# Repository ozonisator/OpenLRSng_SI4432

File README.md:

OpenLRSng Empfänger mit SI4432 Breakoutboard. Kompatibel zu "DTFUHF 4ch RX"

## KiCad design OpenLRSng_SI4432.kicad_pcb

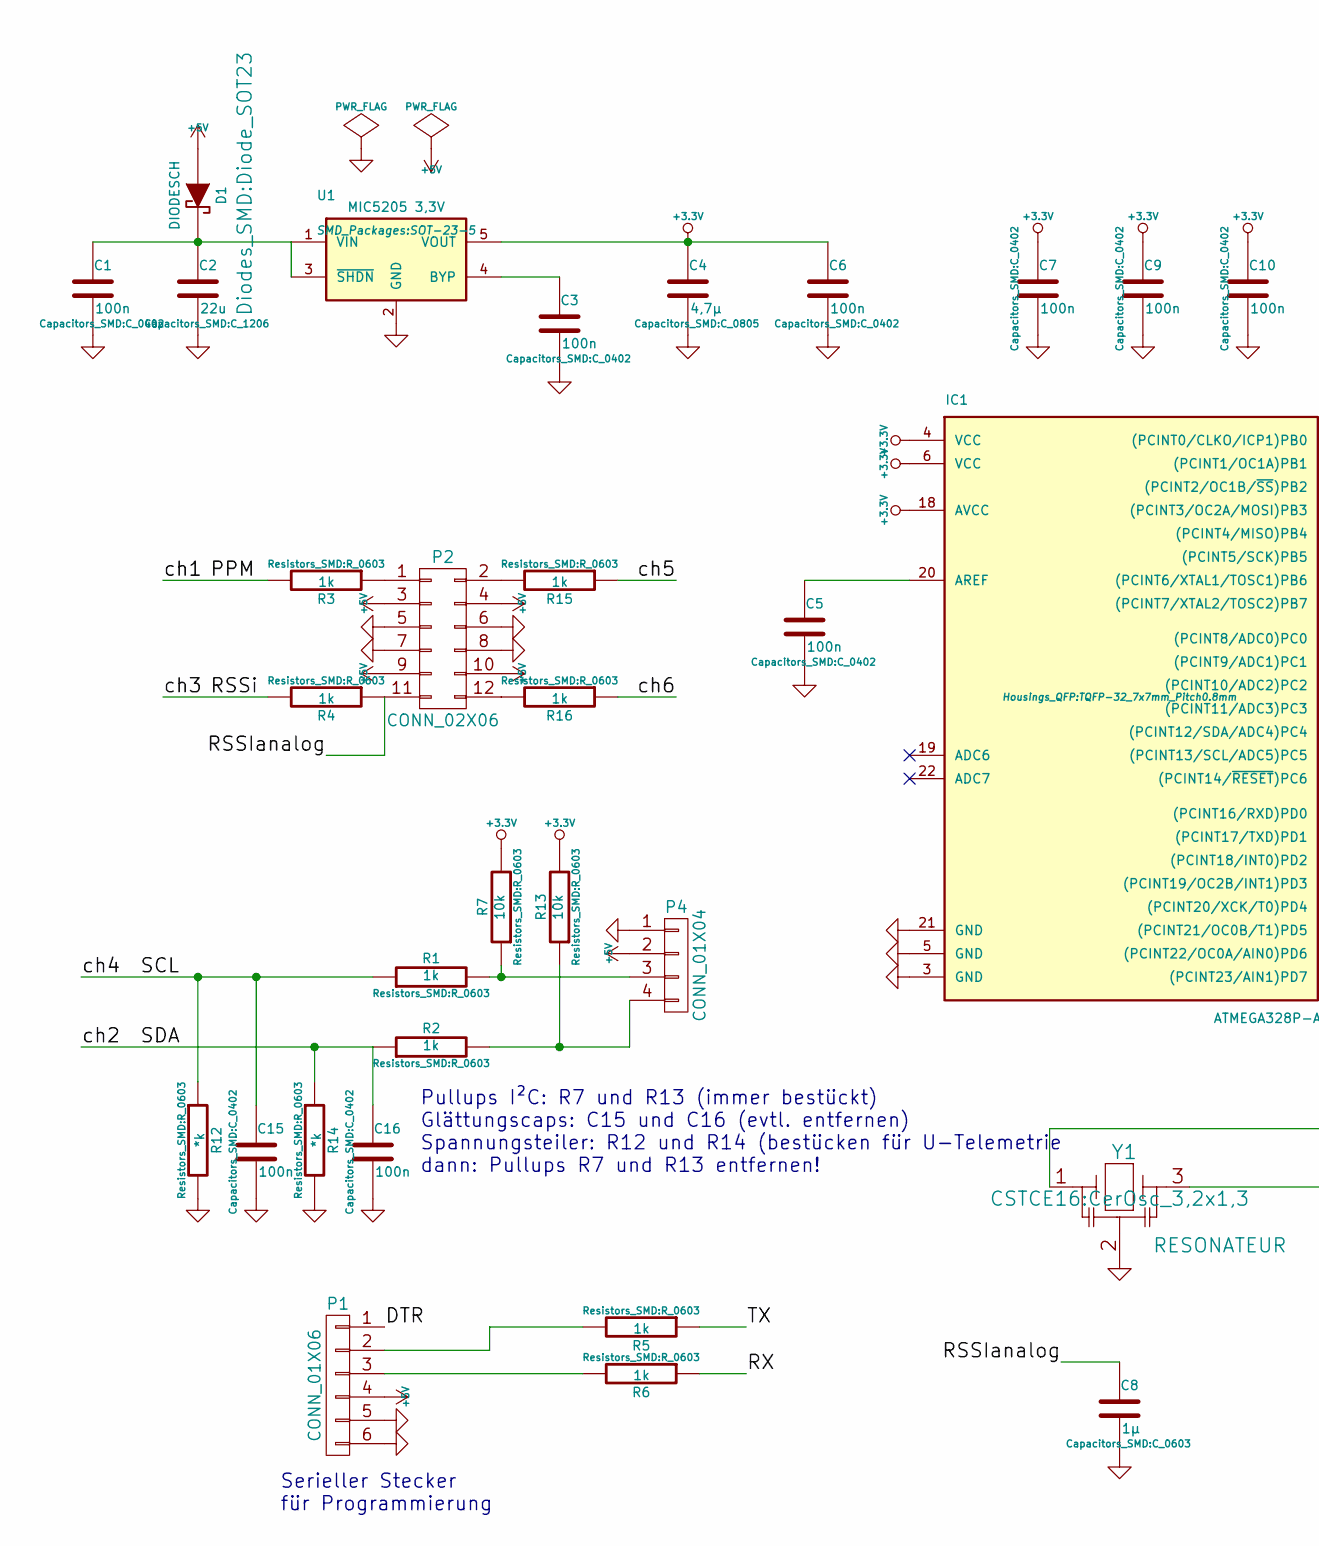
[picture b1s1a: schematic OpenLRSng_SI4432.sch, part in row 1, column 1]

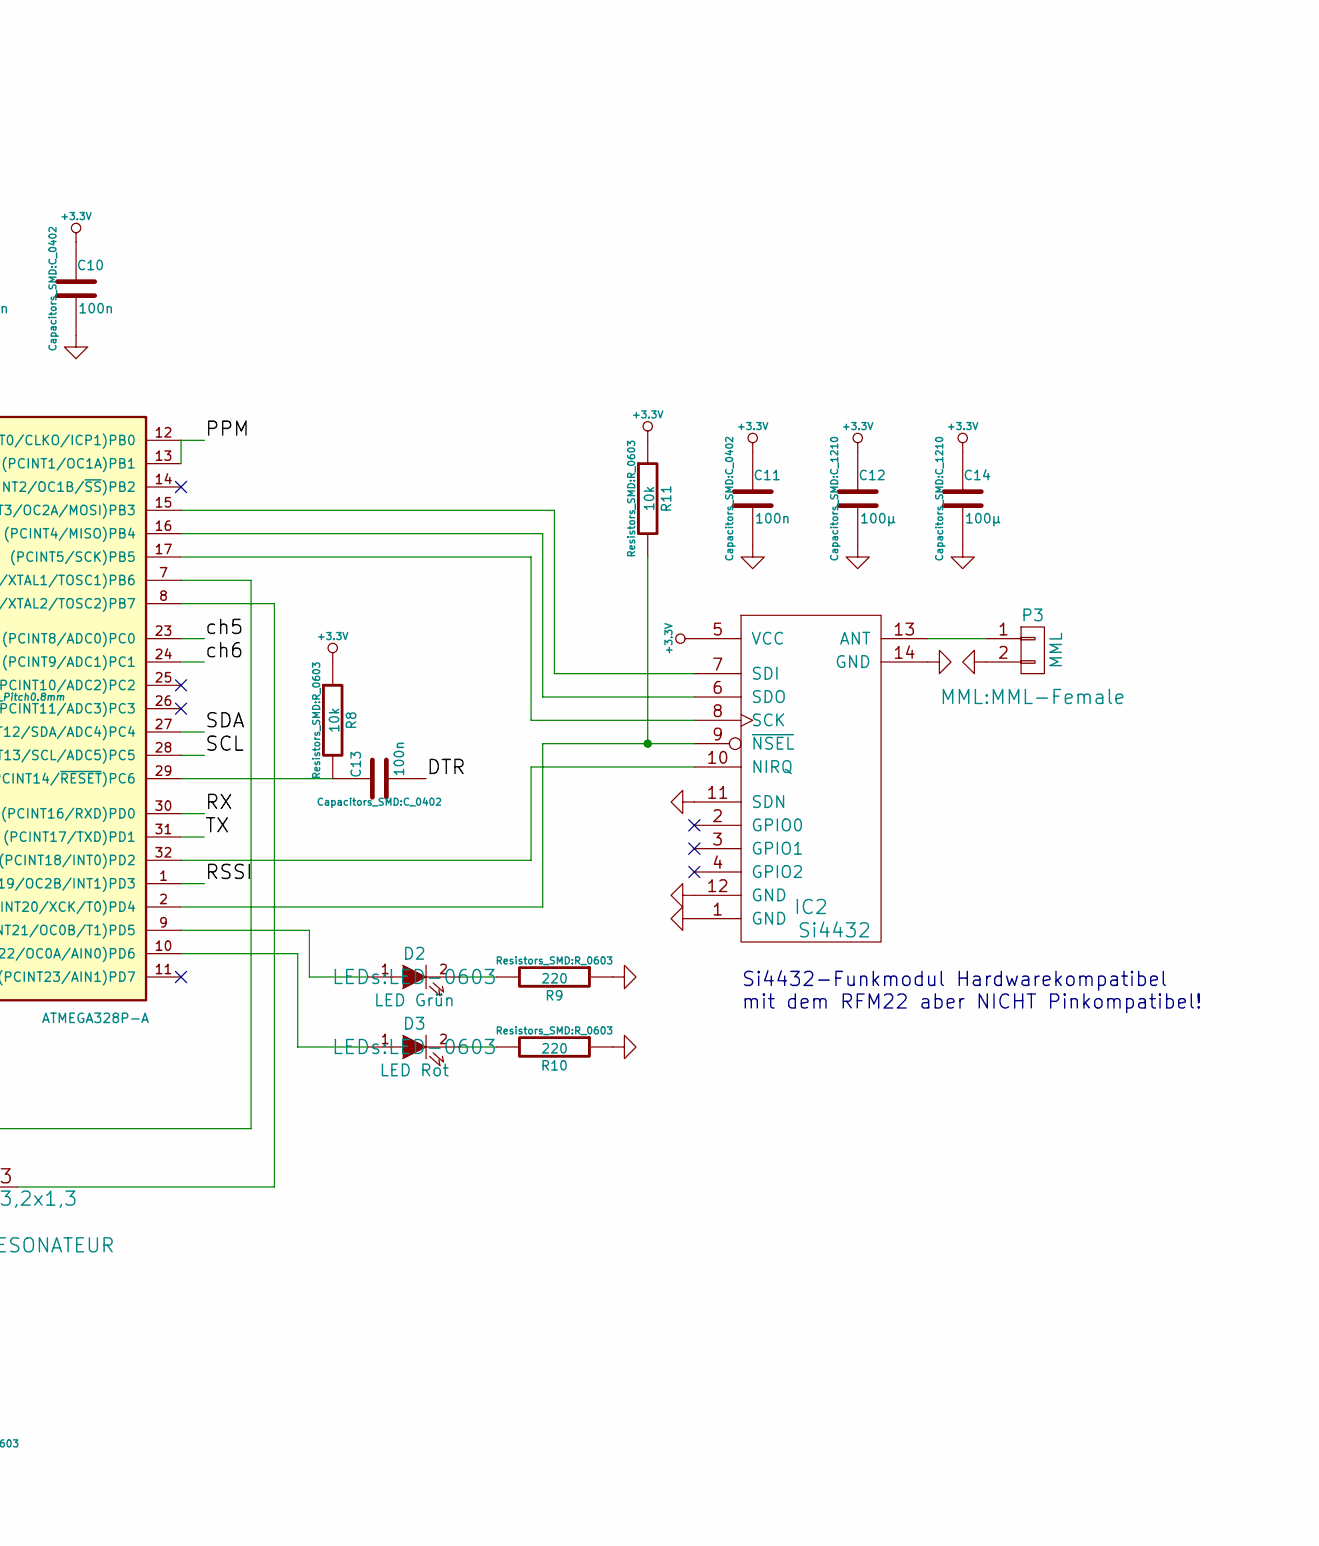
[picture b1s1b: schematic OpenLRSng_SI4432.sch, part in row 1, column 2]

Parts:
C1, C3, C5, C6, C7, C9, C10, C11, C13, C15, C16: 100n; C_0402
C2: 22u; C_1206
C4: 4,7µ; C_0805
C8: 1µ; C_0603
C12, C14: 100µ; C_1210
D1: DIODESCH; Diode_SOT23
D2: LED Grün; LED-0603
D3: LED Rot; LED-0603
IC1: ATMEGA328P-A; TQFP-32_7x7mm_Pitch0.8mm
IC2: Si4432; SI4432_Module
P1: CONN_01X06; Pin_Header_Straight_1x06
P2: CONN_02X06; Pin_Header_Angled_2x06
P3: MML; MML-Female
P4: CONN_01X04; Connector_Molex_PicoBlade_53261-0471
R1, R2, R3, R4, R5, R6, R15, R16: 1k; R_0603
R7, R8, R11, R13: 10k; R_0603
R9, R10: 220; R_0603
R12, R14: *k; R_0603
U1: MIC5205 3,3V; SOT-23-5
Y1: RESONATEUR; CerOsc_3,2x1,3

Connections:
+3.3V: C4.1, C6.1, C7.1, C9.1, C10.1, C11.1, C12.1, C14.1, IC1.4 (VCC), IC1.6 (VCC), IC1.18 (AVCC), IC2.5 (VCC), R7.2, R8.1, R11.1, R13.2, U1.5 (VOUT)
+5V: D1.1 (A), P1.4, P2.3, P2.4, P2.9, P2.10, P4.2
/DTR: C13.2, P1.1
/PPM: IC1.12 ((PCINT0/CLKO/ICP1)PB0), IC1.13 ((PCINT1/OC1A)PB1), R3.2
/RSSI: IC1.1 ((PCINT19/OC2B/INT1)PD3), R4.2
/RSSIanalog: C8.1, P2.11, R4.1
/RX: IC1.30 ((PCINT16/RXD)PD0), R6.1
/SCL: C15.1, IC1.28 ((PCINT13/SCL/ADC5)PC5), R1.1, R12.1
/SDA: C16.1, IC1.27 ((PCINT12/SDA/ADC4)PC4), R2.1, R14.1
/TX: IC1.31 ((PCINT17/TXD)PD1), R5.1
/ch5: IC1.23 ((PCINT8/ADC0)PC0), R15.1
/ch6: IC1.24 ((PCINT9/ADC1)PC1), R16.1
GND: C1.2, C2.2, C3.2, C4.2, C5.2, C6.2, C7.2, C8.2, C9.2, C10.2, C11.2, C12.2, C14.2, C15.2, C16.2, IC1.3 (GND), IC1.5 (GND), IC1.21 (GND), IC2.1 (GND), IC2.11 (SDN), IC2.12 (GND), IC2.14 (GND), P1.5, P1.6, P2.5, P2.6, P2.7, P2.8, P3.2, P4.1, R9.1, R10.1, R12.2, R14.2, U1.2 (GND), Y1.2
unnamed: C1.1, C2.1, D1.2 (K), U1.1 (VIN), U1.3 (~SHDN~)
unnamed: C3.1, U1.4 (BYP)
unnamed: C5.1, IC1.20 (AREF)
unnamed: C13.1, IC1.29 ((PCINT14/~RESET~)PC6), R8.2
unnamed: D2.1 (A), IC1.9 ((PCINT21/OC0B/T1)PD5)
unnamed: D2.2 (K), R9.2
unnamed: D3.1 (A), IC1.10 ((PCINT22/OC0A/AIN0)PD6)
unnamed: D3.2 (K), R10.2
unnamed: IC1.2 ((PCINT20/XCK/T0)PD4), IC2.9 (~NSEL), R11.2
unnamed: IC1.7 ((PCINT6/XTAL1/TOSC1)PB6), Y1.1
unnamed: IC1.8 ((PCINT7/XTAL2/TOSC2)PB7), Y1.3
unnamed: IC1.15 ((PCINT3/OC2A/MOSI)PB3), IC2.7 (SDI)
unnamed: IC1.16 ((PCINT4/MISO)PB4), IC2.6 (SDO)
unnamed: IC1.17 ((PCINT5/SCK)PB5), IC2.8 (SCK)
unnamed: IC1.32 ((PCINT18/INT0)PD2), IC2.10 (NIRQ)
unnamed: IC2.13 (ANT), P3.1
unnamed: P1.2, R5.2
unnamed: P1.3, R6.2
unnamed: P2.1, R3.1
unnamed: P2.2, R15.2
unnamed: P2.12, R16.2
unnamed: P4.3, R1.2, R7.1
unnamed: P4.4, R2.2, R13.1

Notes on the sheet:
Serieller Stecker für Programmierung
Si4432-Funkmodul Hardwarekompatibel mit dem RFM22 aber NICHT Pinkompatibel!
Pullups I²C: R7 und R13 (immer bestückt) Glättungscaps: C15 und C16 (evtl. entfernen) Spannungsteiler: R12 und R14 (bestücken für U-Telemetrie dann: Pullups R7 und R13 entfernen!

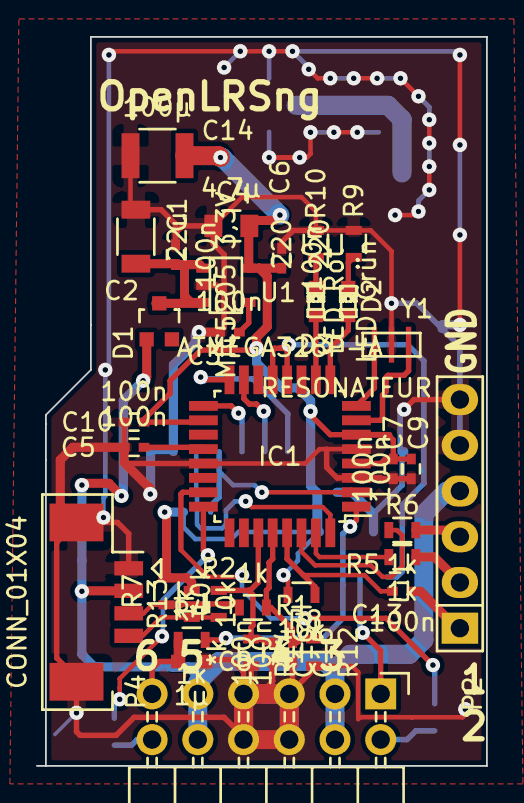
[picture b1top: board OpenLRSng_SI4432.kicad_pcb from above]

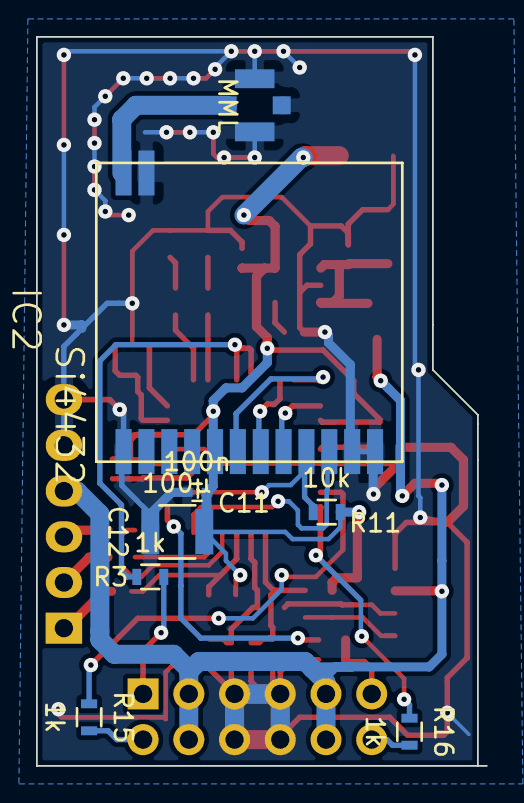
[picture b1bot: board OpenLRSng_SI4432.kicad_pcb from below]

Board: 2 copper layers, 25.0 x 40.5 mm, 43 parts (8 on the bottom side), 36 nets.

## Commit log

2015-02-01 OpenLRSng Empfänger mit Si4432 Breakout Board, Layout identisch zu DTFUHF 4 Kanal Empfänger
2015-02-01 Readme hinzugefügt
2015-02-03 100uF Cap von 1206 auf 1210 geändert
2015-02-03 gitignore-datei hinzugefügt, damit Backupdateien nicht mehr im repo rumliegen.
2015-02-04 -SI4432 Bibliothek gefixt (Pin14 GND vergessen im Schaltplan) -DuKo Kupferfläche vergrößert -zusätzlich noch einmal 100uF Kerko an die 3,3V Rail -Via Stichting an der Massefläche
2015-02-04 entferne redundanz...
2015-02-05 Schaltplan aktualisiert
2015-02-05 gerber ordner richtig angelegt
2015-02-06 4 Kanal auf 6 Kanal umgebaut und leicht optimiert
2015-02-06 pdf-Schaltplan aktualisiert
2015-02-24 Von 6 auf 4 Kanäle reduziert, I2C oder Analog in der Zusätzliche Kanäle über PicoBlade, Spannungsteiler/Pullup/Schutzwiderstandspads
2015-02-24 Tiefpassfilter Cap an den Analog Inputs nachgerüstet
2015-02-24 Spannungsteiler korrigiert...
2015-02-24 Schaltplan finalisiert, I²C-Stecker nach APM-Standard angebracht
2015-02-27 picoblade dazu und layout etwas weiter. noch unfertig.
2015-02-28 I²C Stecker im APM-Layout dazugefügt und Layout soweit fertig gemacht
2015-02-28 schaltplan als pdf exportiert und aktualisiert
2015-03-22 code als submodul dazugefügt und ein paar Bilder eines Moduls eingbaut
